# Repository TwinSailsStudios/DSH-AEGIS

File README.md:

# DSH-AEGIS

Image of PCB routing and tracing

image of schematic

Image of case + accessories (SD card case, micro sd card case, case cowl, stand, and sd/micro sd card storage)

Image of 3d model

https://github.com/user-attachments/assets/2e60c4a9-2eaf-4800-a794-9d0f289f58ca
Video of 3d model
### UPDATE NOTICE:
alr so i added step/stp files in the hardware folder in a zip file since they were too big for regular uploads (terminal limit is 100mb), i also made the pcb more compact, but the i didnt update the cover image, so you'll have to download the pcb file.

A physical password manager. ESP32-S3, a tiny OLED, six buttons, and an SD card.
Plugs into your computer over USB-C and *types* your passwords for you.

> **Status: designed, not built.** The schematic and PCB are done, the firmware
> is written. I haven't ordered the board yet because I'm paying for this stuff
> myself and PCBs cost money. Everything here is verified in KiCad, not on a
> bench. I'll update this when I can afford to fab it.

## why

I was using the same password on like nine different sites. Which is bad. Every
password manager I looked at wanted me to trust a company with all of it, and I
didn't love that either. So: keep them on an SD card, in my pocket, encrypted.

## what it does

- Locks behind a PIN you enter on the buttons
- Vault is encrypted on the SD card with AES-256
- Types the password straight into the login box over USB
- Can do username → Tab → password to fill a whole form
- Generates strong random passwords
- Auto-locks after 60s if you walk away

The typing thing is the whole point. The ESP32-S3 has **native USB**, so the board
doesn't *pretend* to be a keyboard — your computer genuinely thinks a keyboard got
plugged in. No drivers, no app. Works on any machine you walk up to.

## hardware

| part | what it does |
|---|---|
| ESP32-S3-WROOM-1 | the brain. picked for native USB |
| SSD1306 128x32 OLED | the screen (I2C) |
| 6x tactile switches | the controls |
| microSD module | where the vault lives (SPI) |
| USB-C receptacle | power + keyboard |
| AMS1117-3.3 | 5V → 3.3V |
| 2x 5.1K resistors | CC pins, so USB-C actually gives you power |

## pinout

| pin | goes to |
|---|---|
| IO0–IO5 | RECORD, SAVE, PLAY, SCROLL-L, SELECT, SCROLL-R |
| IO6 / IO7 | OLED SCL / SDA |
| IO35–IO38 | SD CS / MOSI / SCK / MISO |

**Heads up on IO35–37.** On an ESP32-S3 module with **octal (R8) PSRAM**, those
three pins are wired to the PSRAM die internally and you can't use them as GPIO.
This board only works with a **no-PSRAM or quad-PSRAM** module. If you build it,
check the part number, and set **PSRAM: Disabled** in the Arduino IDE — leave it
on OPI and the chip claims those pins at boot, before your code runs, and the SD
card silently never mounts.

## how you'd use it

Enter your PIN. Scroll to the login you want with the arrow buttons. Click into
whatever password box you're filling out on your computer. Hit **PLAY**. Done.

**SELECT** opens a menu with more options: type just the password, type
username+Tab+password, show the password on screen, or delete it.

Adding a new entry is the weak spot right now — you press **RECORD** and it hands
off to the serial monitor, where you send `label⇥username⇥password`. A password
manager that needs a computer to set up is a bit embarrassing and I want to fix
it. (Put `*` as the password and it generates one for you.)

Then hit **SAVE** to encrypt it and write it to the card.

## the crypto

Boring on purpose. Your PIN goes through PBKDF2-HMAC-SHA256 (60,000 rounds, random
salt) to turn 4 digits into a real key. Vault is AES-256-CBC. There's an HMAC over
the ciphertext, so a wrong PIN fails the check and the device never even attempts
to decrypt. Salt and IV are fresh every save.

I did not invent any of this. Inventing your own crypto is how you become a
cautionary example in someone's blog post.

## build it yourself

Firmware is in `firmware/`. You need the **U8g2** library; everything else ships
with the ESP32 Arduino core.

Board settings:
- Board: ESP32S3 Dev Module
- USB CDC On Boot: **Enabled**
- USB Mode: **USB-OTG (TinyUSB)**
- PSRAM: **Disabled** (see the IO35 warning above)

KiCad project is in `hardware/`.

## what's not done

- **Never physically built.** Simulated and verified in KiCad only.
- A 4-digit PIN is 10,000 combinations. The PBKDF2 rounds slow an attacker down a
  lot but it's not amazing if someone steals the card and is patient.
- No lockout after repeated wrong guesses.
- Can't add entries on the device, needs serial.
- No way to change your PIN without wiping everything.
- Case is modelled in Tinkercad but not printed.

## AI use
I used gemini to help with some kicad features and trying to debug a probelm with exporting my 3d model of my pcb
I used Claude to help write the firmware and to talk through design decisions
(pin conflicts, how to structure the vault encryption). The schematic, PCB layout, 
3D model, and this README are mine. the firmware, im not gonna act like i wrote it from scratch, it was more like using claude to frankenstien my code togetehr into a working firmware, since i haventbuilt ts irl yet, if any of yall try PLEASE lmk if theres any code problems, thx:)

EDIT: I also gave claude access to organize all the files

## license

MIT. do whatever.

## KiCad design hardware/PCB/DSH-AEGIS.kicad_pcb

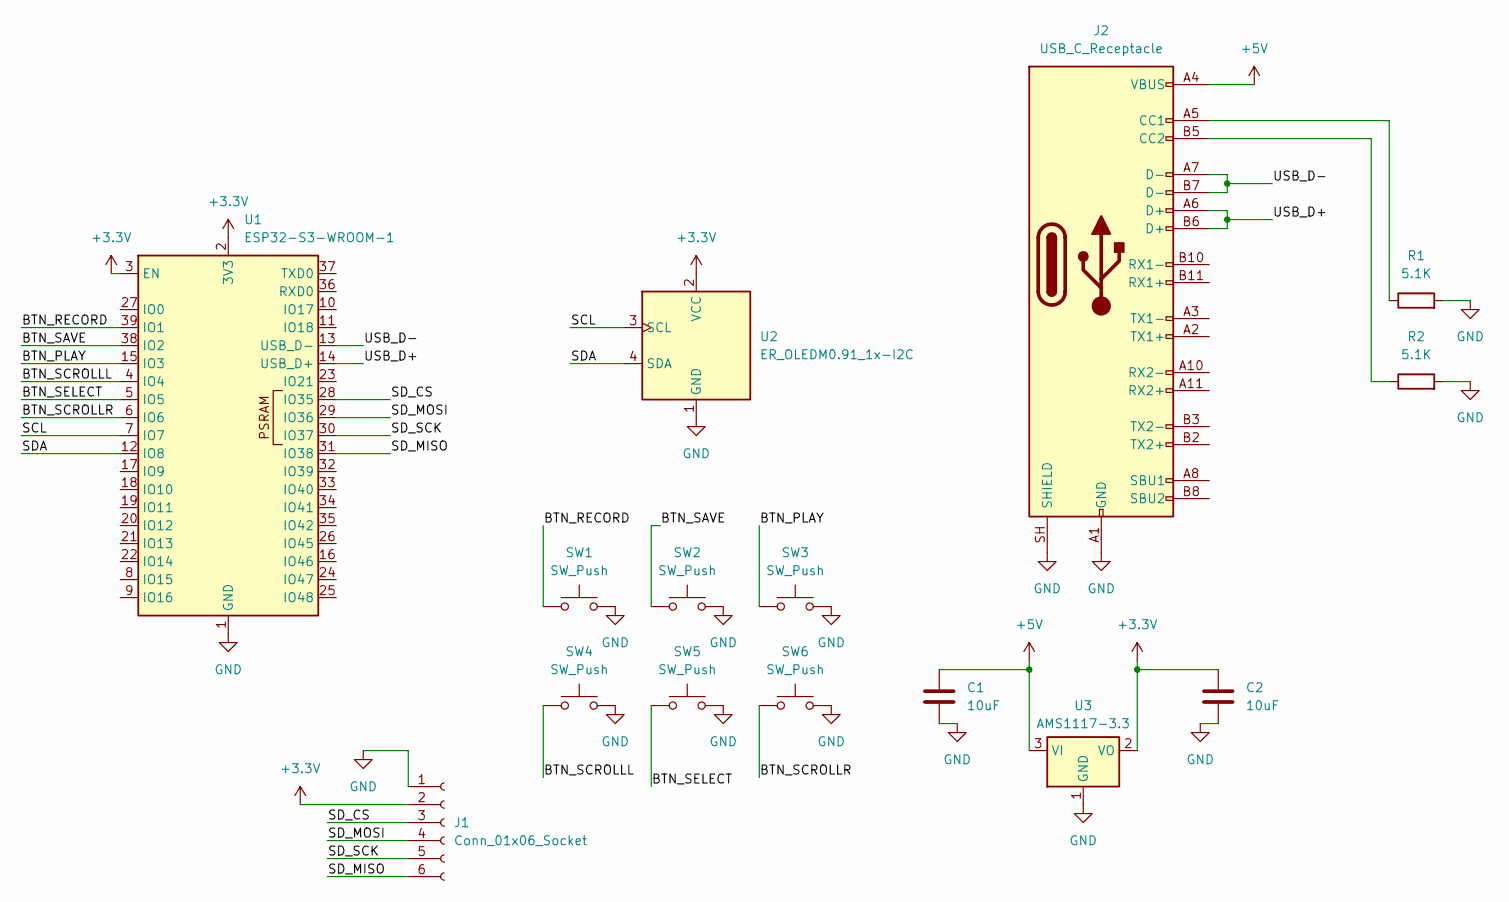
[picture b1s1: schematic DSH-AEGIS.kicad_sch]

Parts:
C1, C2: 10uF; C_0805_2012Metric
J1: Conn_01x06_Socket; PinSocket_1x06_P2.54mm_Vertical
J2: USB_C_Receptacle; USB_C_Receptacle_XKB_U262-16XN-4BVC11
R1, R2: 5.1K; R_0805_2012Metric
SW1, SW2, SW3, SW4, SW5, SW6: SW_Push; SW_Cherry_MX_1.00u_PCB
U1: ESP32-S3-WROOM-1
U2: ER_OLEDM0.91_1x-I2C
U3: AMS1117-3.3; SOT-223-3_TabPin2

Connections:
+3.3V: C2.1, J1.2, U1.2 (3V3), U1.3 (EN), U2.2 (VCC), U3.2 (VO)
+5V: C1.1, J2.A4 (VBUS), J2.A9 (VBUS), J2.B4 (VBUS), J2.B9 (VBUS), U3.3 (VI)
/BTN_PLAY: SW3.1, U1.15 (IO3)
/BTN_RECORD: SW1.1, U1.39 (IO1)
/BTN_SAVE: SW2.1, U1.38 (IO2)
/BTN_SCROLLL: SW4.1, U1.4 (IO4)
/BTN_SCROLLR: SW6.1, U1.6 (IO6)
/BTN_SELECT: SW5.1, U1.5 (IO5)
/SCL: U1.7 (IO7), U2.3 (SCL)
/SDA: U1.12 (IO8), U2.4 (SDA)
/SD_CS: J1.3, U1.28 (IO35)
/SD_MISO: J1.6, U1.31 (IO38)
/SD_MOSI: J1.4, U1.29 (IO36)
/SD_SCK: J1.5, U1.30 (IO37)
/USB_D+: J2.A6 (D+), J2.B6 (D+), U1.14 (USB_D+)
/USB_D-: J2.A7 (D-), J2.B7 (D-), U1.13 (USB_D-)
GND: C1.2, C2.2, J1.1, J2.A1 (GND), J2.A12 (GND), J2.B1 (GND), J2.B12 (GND), J2.SH (SHIELD), R1.2, R2.2, SW1.2, SW2.2, SW3.2, SW4.2, SW5.2, SW6.2, U1.1 (GND), U1.40 (GND), U1.41 (GND), U2.1 (GND), U3.1 (GND)
unnamed: J2.A5 (CC1), R1.1
unnamed: J2.B5 (CC2), R2.1

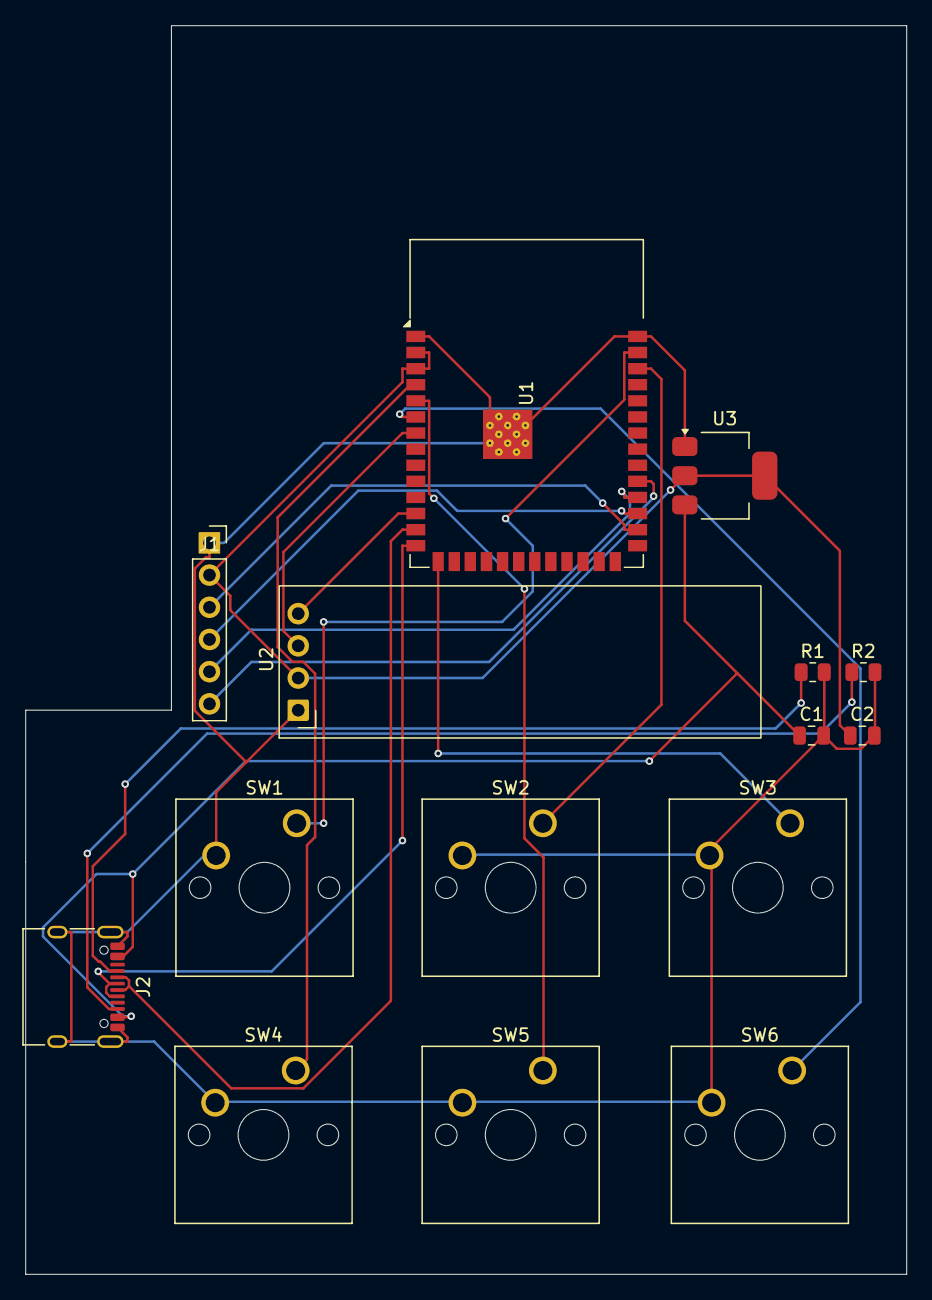
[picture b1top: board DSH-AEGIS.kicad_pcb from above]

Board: 2 copper layers, 69.5 x 98.5 mm, 15 parts (0 on the bottom side), 19 nets.

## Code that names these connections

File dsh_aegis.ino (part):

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// module those pins are wired to the PSRAM die and are unusable. This build
// targets a module with no PSRAM / quad PSRAM, where they're free GPIO. If you
// ever swap in an R8 part, these three have to move.
#define PIN_SD_CS    35
#define PIN_SD_MOSI  36
#define PIN_SD_SCK   37
#define PIN_SD_MISO  38

/* ----------------------------------------------------------------------------
 *  2. FEEL  —  knobs for behaviour, tune to taste
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  Keyboard.begin();
  USB.begin();

  sdSPI.begin(PIN_SD_SCK, PIN_SD_MISO, PIN_SD_MOSI, PIN_SD_CS);
  bool sdOk = SD.begin(PIN_SD_CS, sdSPI);

  // opening splash
  oled.clearBuffer();
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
